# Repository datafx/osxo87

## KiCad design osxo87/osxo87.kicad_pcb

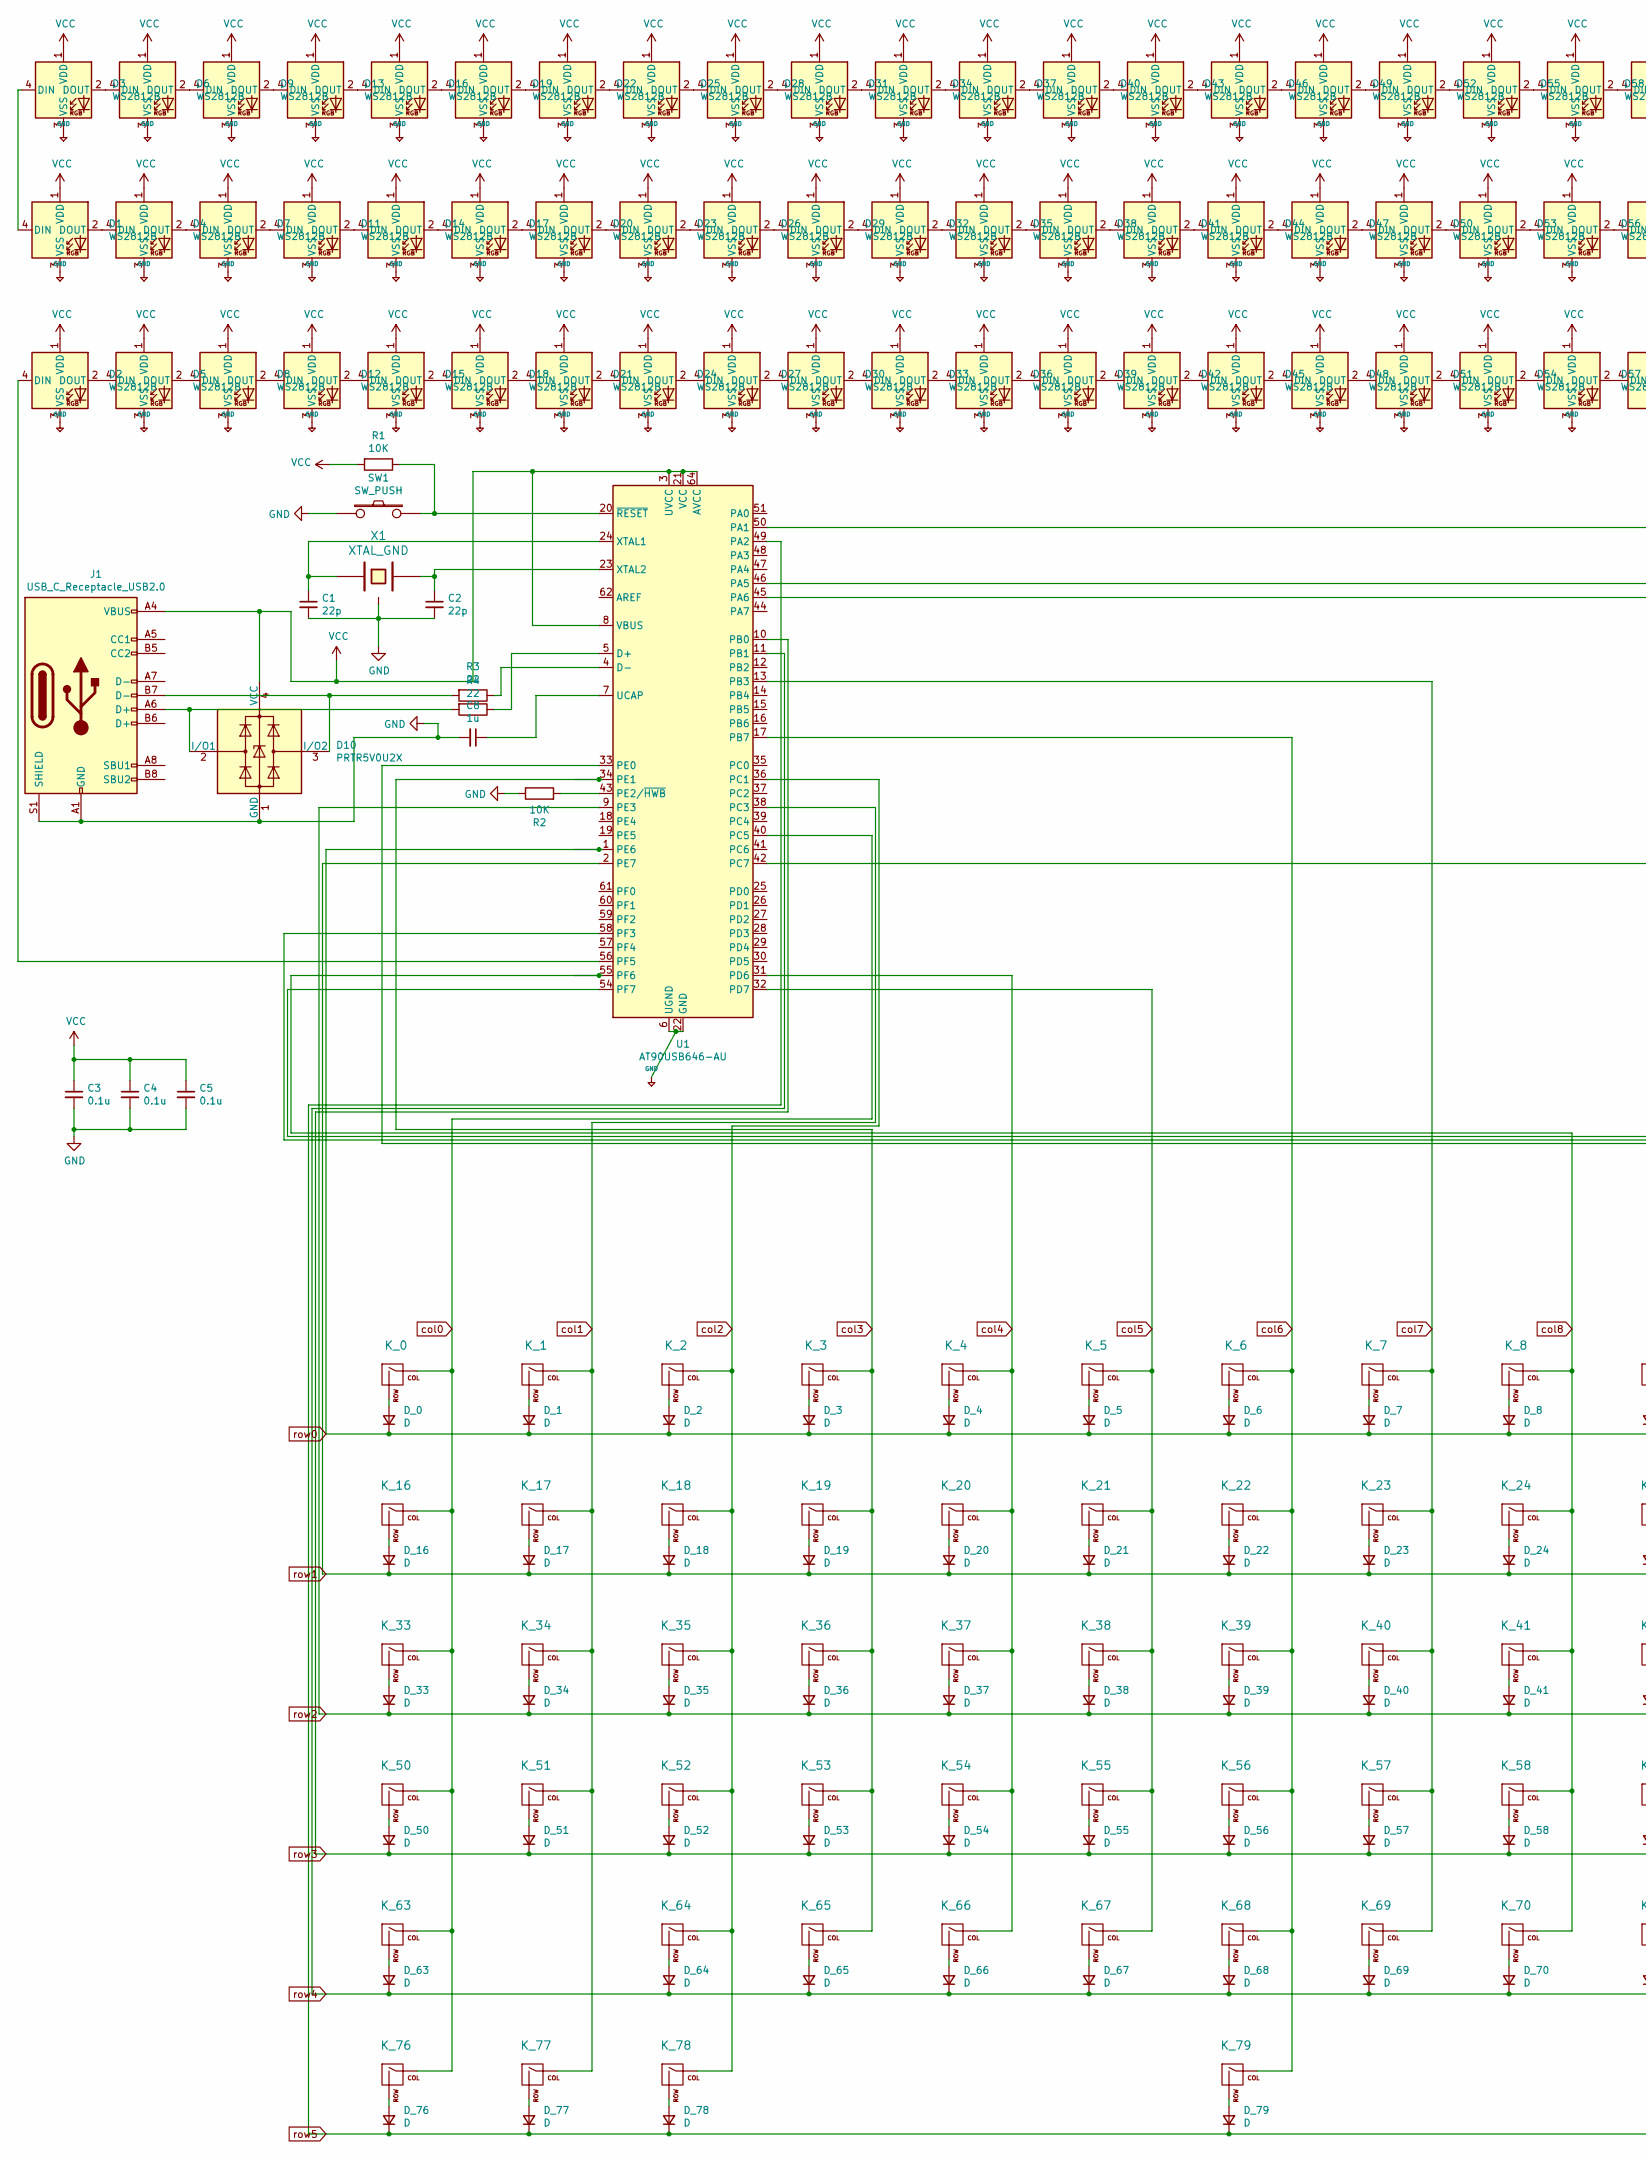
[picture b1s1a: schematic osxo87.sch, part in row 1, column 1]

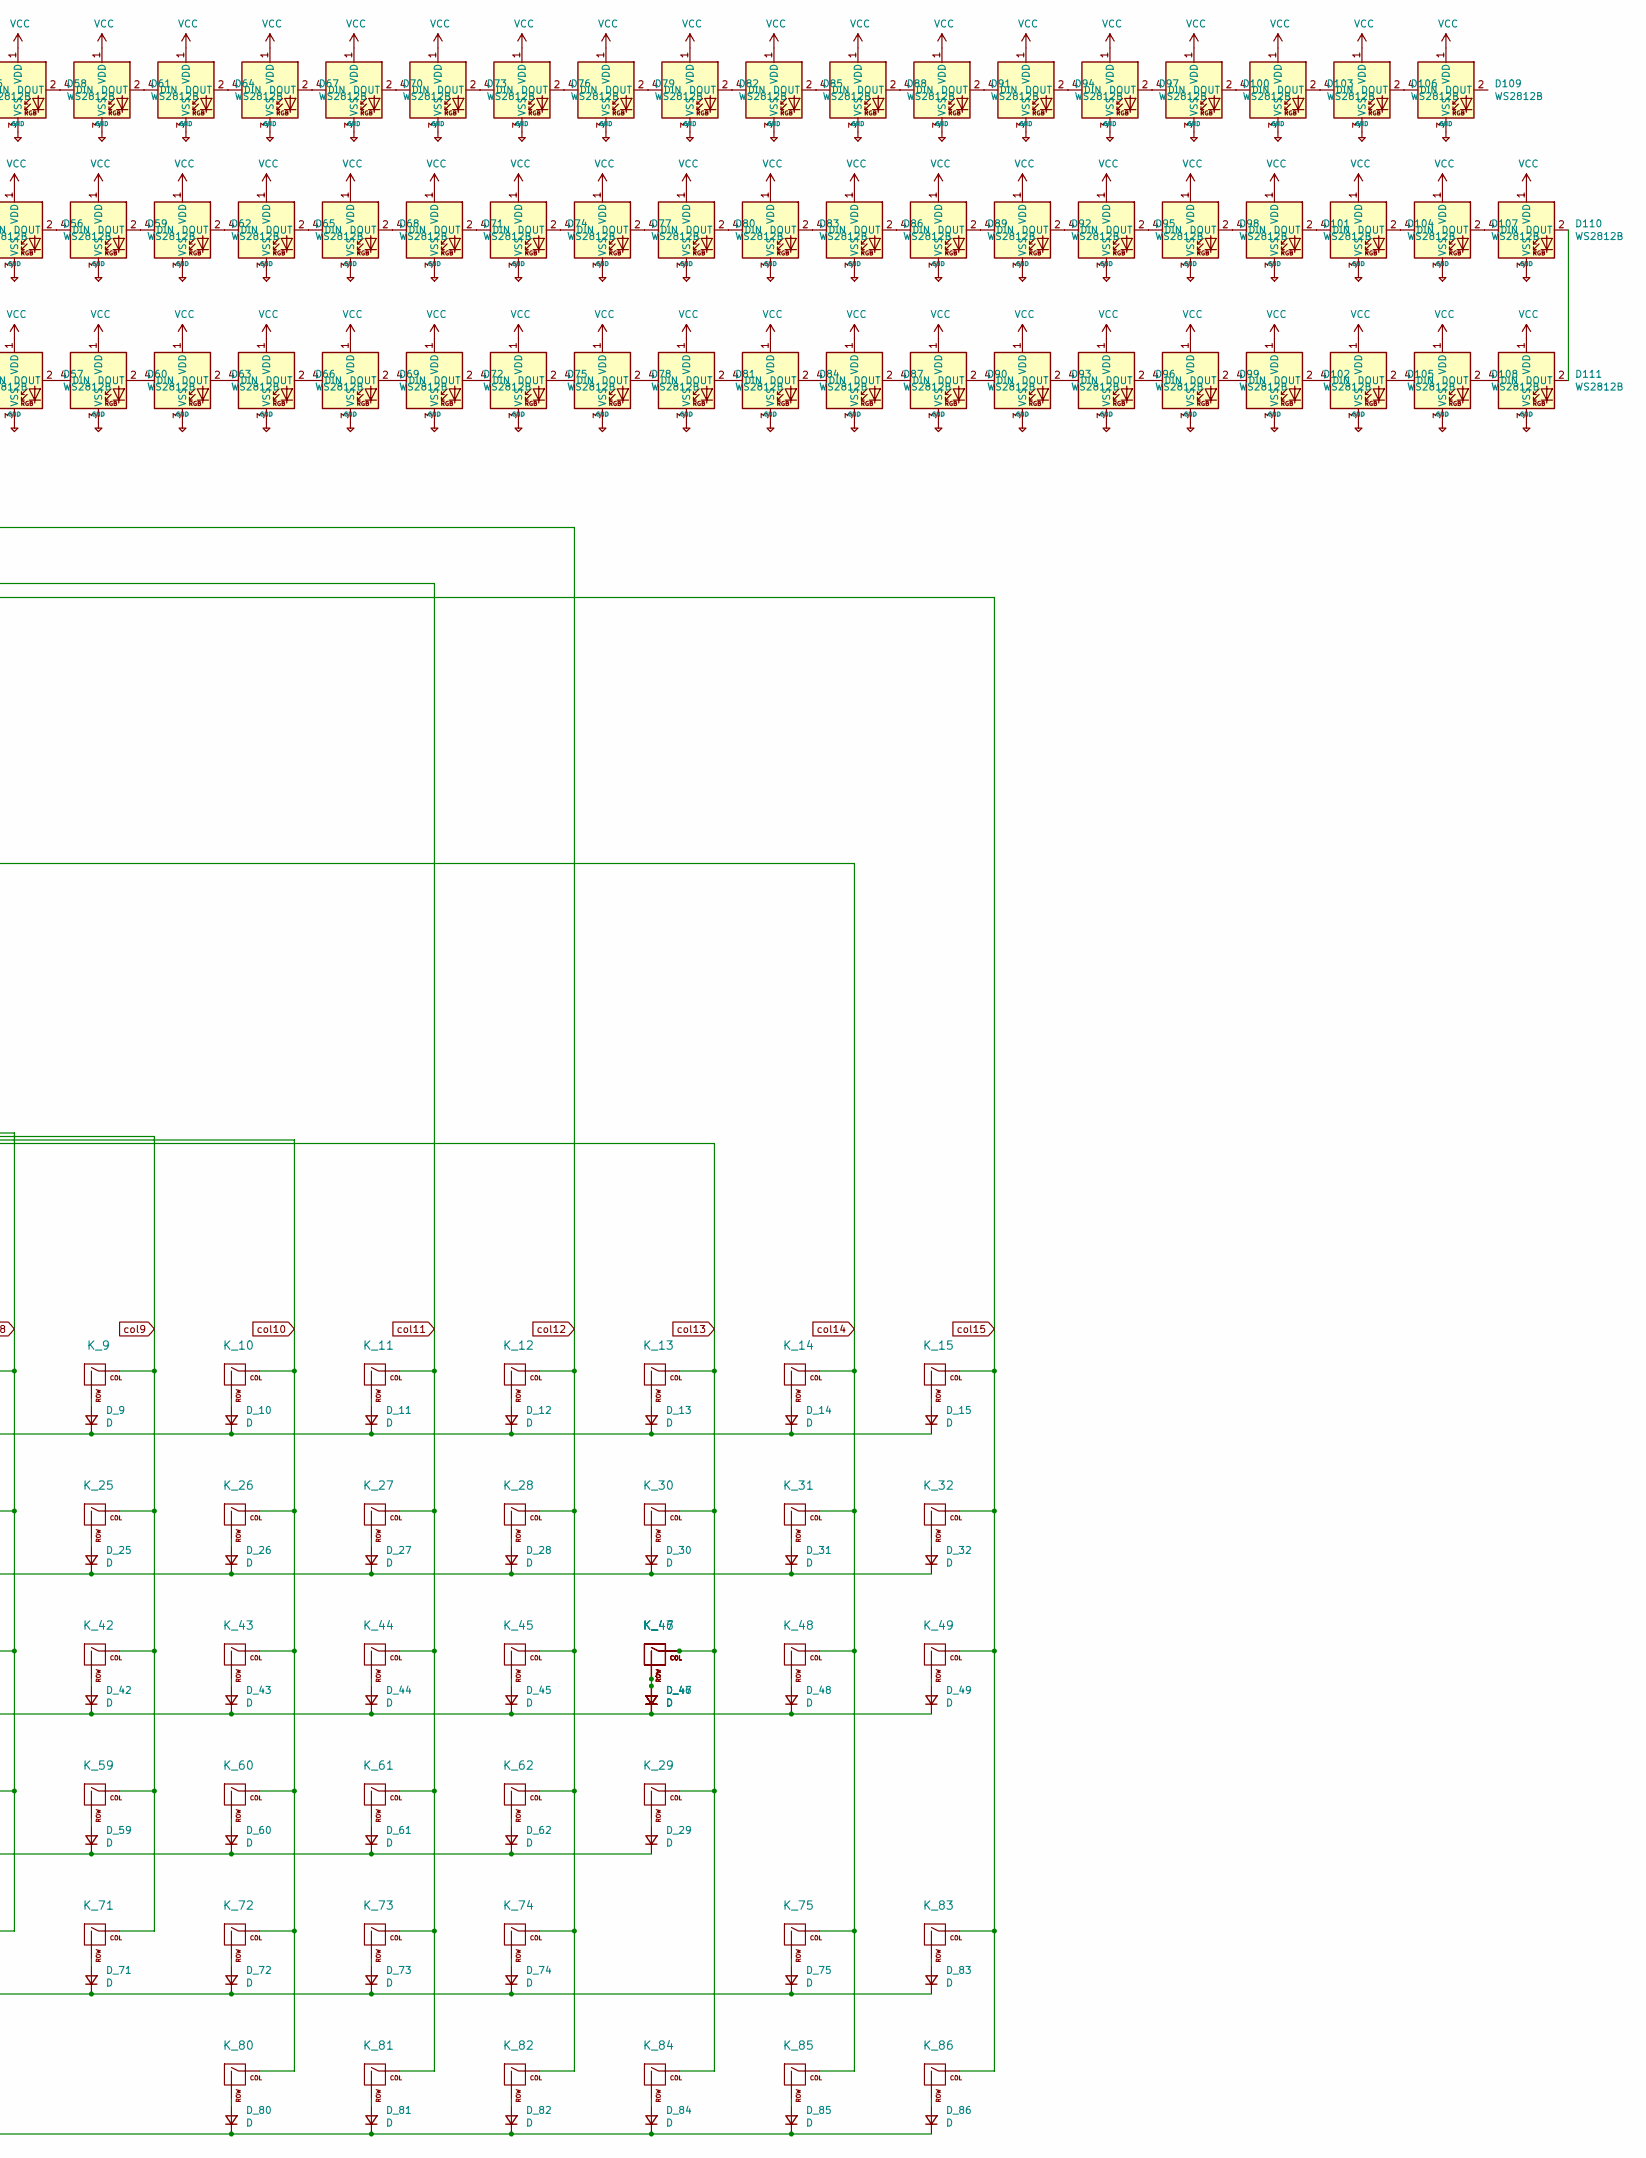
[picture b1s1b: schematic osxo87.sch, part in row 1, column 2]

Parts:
C1, C2: 22p; C_0805_2012Metric
C3, C4, C5: 0.1u; C_0805_2012Metric
C8: 1u; C_0805_2012Metric
D1, D2, D3, D4, D5, D6, D7, D8, D9, D11, D12, D13, D14, D15, D16, D17, D18, D19, D20, D21, D22, D23, D24, D25, D26, D27, D28, D29, D30, D31, D32, D33, D34, D35, D36, D37, D38, D39, D40, D41, D42, D43, D44, D45, D46, D47, D48, D49, D50, D51, D52, D53, D54, D55, D56, D57, D58, D59, D60, D61, D62, D63, D64, D65, D66, D67, D68, D69, D70, D71, D72, D73, D74, D75, D76, D77, D78, D79, D80, D81, D82, D83, D84, D85, D86, D87, D88, D89, D90, D91, D92, D93, D94, D95, D96, D97, D98, D99, D100, D101, D102, D103, D104, D105, D106, D107, D108, D109, D110, D111: WS2812B; LED_WS2812B_PLCC4_5.0x5.0mm_P3.2mm
D10: PRTR5V0U2X; SOT-143
D_0, D_1, D_2, D_3, D_4, D_5, D_6, D_7, D_8, D_9, D_10, D_11, D_12, D_13, D_14, D_15, D_16, D_17, D_18, D_19, D_20, D_21, D_22, D_23, D_24, D_25, D_26, D_27, D_28, D_29, D_30, D_31, D_32, D_33, D_34, D_35, D_36, D_37, D_38, D_39, D_40, D_41, D_42, D_43, D_44, D_45, D_46, D_47, D_48, D_49, D_50, D_51, D_52, D_53, D_54, D_55, D_56, D_57, D_58, D_59, D_60, D_61, D_62, D_63, D_64, D_65, D_66, D_67, D_68, D_69, D_70, D_71, D_72, D_73, D_74, D_75, D_76, D_77, D_78, D_79, D_80, D_81, D_82, D_83, D_84, D_85, D_86: D; D_SOD-123
J1: USB_C_Receptacle_USB2.0; USB_C_Receptacle_Palconn_UTC16-G
K_0, K_1, K_2, K_3, K_4, K_5, K_6, K_7, K_8, K_9, K_10, K_11, K_12, K_13, K_14, K_15, K_16, K_17, K_18, K_19, K_20, K_21, K_22, K_23, K_24, K_25, K_26, K_27, K_28, K_30, K_31, K_32, K_34, K_35, K_36, K_37, K_38, K_39, K_40, K_41, K_42, K_43, K_44, K_45, K_47, K_48, K_49, K_51, K_52, K_53, K_54, K_55, K_56, K_57, K_58, K_59, K_60, K_61, K_64, K_65, K_66, K_67, K_68, K_69, K_70, K_71, K_72, K_73, K_75, K_84, K_85, K_86: KEYSW; MX-1U-NoLED
K_29: KEYSW; MX-2U-NoLED
K_33, K_46: KEYSW; MX-1.5U-NoLED
K_50: KEYSW; MX-1.75U-NoLED
K_62, K_63: KEYSW; MX-2.25U-NoLED
K_74: KEYSW; MX-2.75U-NoLED
K_76, K_77, K_78, K_80, K_81, K_82, K_83: KEYSW; MX-1.25U-NoLED
K_79: KEYSW; MX-6.25U-NoLED
R1, R2: 10K; R_0805_2012Metric
R3, R4: 22; R_0805_2012Metric
SW1: SW_PUSH; Panasonic_EVQPUJ_EVQPUA
U1: AT90USB646-AU; TQFP-64_14x14mm_P0.8mm
X1: XTAL_GND; Crystal_SMD_0603-4Pin_6.0x3.5mm

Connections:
unnamed: C1.1, U1.24 (XTAL1), X1.1
unnamed: C2.1, U1.23 (XTAL2), X1.2
unnamed: C8.1, U1.7 (UCAP)
unnamed: D1.2 (DOUT), D4.4 (DIN)
unnamed: D1.4 (DIN), D3.4 (DIN)
unnamed: D2.2 (DOUT), D5.4 (DIN)
unnamed: D2.4 (DIN), U1.56 (PF5)
unnamed: D3.2 (DOUT), D6.4 (DIN)
unnamed: D4.2 (DOUT), D7.4 (DIN)
unnamed: D5.2 (DOUT), D8.4 (DIN)
unnamed: D6.2 (DOUT), D9.4 (DIN)
unnamed: D10.2 (I/O1), J1.A6 (D+), R4.2
unnamed: D10.3 (I/O2), J1.B7 (D-), R3.2
unnamed: D11.2 (DOUT), D14.4 (DIN)
unnamed: D7.2 (DOUT), D11.4 (DIN)
unnamed: D12.2 (DOUT), D15.4 (DIN)
unnamed: D8.2 (DOUT), D12.4 (DIN)
unnamed: D13.2 (DOUT), D16.4 (DIN)
unnamed: D9.2 (DOUT), D13.4 (DIN)
unnamed: D14.2 (DOUT), D17.4 (DIN)
unnamed: D15.2 (DOUT), D18.4 (DIN)
unnamed: D16.2 (DOUT), D19.4 (DIN)
unnamed: D17.2 (DOUT), D20.4 (DIN)
unnamed: D18.2 (DOUT), D21.4 (DIN)
unnamed: D19.2 (DOUT), D22.4 (DIN)
unnamed: D20.2 (DOUT), D23.4 (DIN)
unnamed: D21.2 (DOUT), D24.4 (DIN)
unnamed: D22.2 (DOUT), D25.4 (DIN)
unnamed: D23.2 (DOUT), D26.4 (DIN)
unnamed: D24.2 (DOUT), D27.4 (DIN)
unnamed: D25.2 (DOUT), D28.4 (DIN)
unnamed: D26.2 (DOUT), D29.4 (DIN)
unnamed: D27.2 (DOUT), D30.4 (DIN)
unnamed: D28.2 (DOUT), D31.4 (DIN)
unnamed: D29.2 (DOUT), D32.4 (DIN)
unnamed: D30.2 (DOUT), D33.4 (DIN)
unnamed: D31.2 (DOUT), D34.4 (DIN)
unnamed: D32.2 (DOUT), D35.4 (DIN)
unnamed: D33.2 (DOUT), D36.4 (DIN)
unnamed: D34.2 (DOUT), D37.4 (DIN)
unnamed: D35.2 (DOUT), D38.4 (DIN)
unnamed: D36.2 (DOUT), D39.4 (DIN)
unnamed: D37.2 (DOUT), D40.4 (DIN)
unnamed: D38.2 (DOUT), D41.4 (DIN)
unnamed: D39.2 (DOUT), D42.4 (DIN)
unnamed: D40.2 (DOUT), D43.4 (DIN)
unnamed: D41.2 (DOUT), D44.4 (DIN)
unnamed: D42.2 (DOUT), D45.4 (DIN)
unnamed: D43.2 (DOUT), D46.4 (DIN)
unnamed: D44.2 (DOUT), D47.4 (DIN)
unnamed: D45.2 (DOUT), D48.4 (DIN)
unnamed: D46.2 (DOUT), D49.4 (DIN)
unnamed: D47.2 (DOUT), D50.4 (DIN)
unnamed: D48.2 (DOUT), D51.4 (DIN)
unnamed: D49.2 (DOUT), D52.4 (DIN)
unnamed: D50.2 (DOUT), D53.4 (DIN)
unnamed: D51.2 (DOUT), D54.4 (DIN)
unnamed: D52.2 (DOUT), D55.4 (DIN)
unnamed: D53.2 (DOUT), D56.4 (DIN)
unnamed: D54.2 (DOUT), D57.4 (DIN)
unnamed: D55.2 (DOUT), D58.4 (DIN)
unnamed: D56.2 (DOUT), D59.4 (DIN)
unnamed: D57.2 (DOUT), D60.4 (DIN)
unnamed: D58.2 (DOUT), D61.4 (DIN)
unnamed: D59.2 (DOUT), D62.4 (DIN)
unnamed: D60.2 (DOUT), D63.4 (DIN)
unnamed: D61.2 (DOUT), D64.4 (DIN)
unnamed: D62.2 (DOUT), D65.4 (DIN)
unnamed: D63.2 (DOUT), D66.4 (DIN)
unnamed: D64.2 (DOUT), D67.4 (DIN)
unnamed: D65.2 (DOUT), D68.4 (DIN)
unnamed: D66.2 (DOUT), D69.4 (DIN)
unnamed: D67.2 (DOUT), D70.4 (DIN)
unnamed: D68.2 (DOUT), D71.4 (DIN)
unnamed: D69.2 (DOUT), D72.4 (DIN)
unnamed: D70.2 (DOUT), D73.4 (DIN)
unnamed: D71.2 (DOUT), D74.4 (DIN)
unnamed: D72.2 (DOUT), D75.4 (DIN)
unnamed: D73.2 (DOUT), D76.4 (DIN)
unnamed: D74.2 (DOUT), D77.4 (DIN)
unnamed: D75.2 (DOUT), D78.4 (DIN)
unnamed: D76.2 (DOUT), D79.4 (DIN)
unnamed: D77.2 (DOUT), D80.4 (DIN)
unnamed: D78.2 (DOUT), D81.4 (DIN)
unnamed: D79.2 (DOUT), D82.4 (DIN)
unnamed: D80.2 (DOUT), D83.4 (DIN)
unnamed: D81.2 (DOUT), D84.4 (DIN)
unnamed: D82.2 (DOUT), D85.4 (DIN)
unnamed: D83.2 (DOUT), D86.4 (DIN)
unnamed: D84.2 (DOUT), D87.4 (DIN)
unnamed: D85.2 (DOUT), D88.4 (DIN)
unnamed: D86.2 (DOUT), D89.4 (DIN)
unnamed: D87.2 (DOUT), D90.4 (DIN)
unnamed: D88.2 (DOUT), D91.4 (DIN)
unnamed: D89.2 (DOUT), D92.4 (DIN)
unnamed: D90.2 (DOUT), D93.4 (DIN)
unnamed: D91.2 (DOUT), D94.4 (DIN)
unnamed: D92.2 (DOUT), D95.4 (DIN)
unnamed: D93.2 (DOUT), D96.4 (DIN)
unnamed: D94.2 (DOUT), D97.4 (DIN)
unnamed: D95.2 (DOUT), D98.4 (DIN)
unnamed: D96.2 (DOUT), D99.4 (DIN)
unnamed: D100.2 (DOUT), D103.4 (DIN)
unnamed: D97.2 (DOUT), D100.4 (DIN)
unnamed: D101.2 (DOUT), D104.4 (DIN)
unnamed: D98.2 (DOUT), D101.4 (DIN)
unnamed: D102.2 (DOUT), D105.4 (DIN)
unnamed: D99.2 (DOUT), D102.4 (DIN)
unnamed: D103.2 (DOUT), D106.4 (DIN)
unnamed: D104.2 (DOUT), D107.4 (DIN)
unnamed: D105.2 (DOUT), D108.4 (DIN)
unnamed: D106.2 (DOUT), D109.4 (DIN)
unnamed: D107.2 (DOUT), D110.4 (DIN)
unnamed: D108.2 (DOUT), D111.4 (DIN)
unnamed: D110.2 (DOUT), D111.2 (DOUT)
unnamed: D_0.2 (A), K_0.2 (ROW)
unnamed: D_1.2 (A), K_1.2 (ROW)
unnamed: D_2.2 (A), K_2.2 (ROW)
unnamed: D_3.2 (A), K_3.2 (ROW)
unnamed: D_4.2 (A), K_4.2 (ROW)
unnamed: D_5.2 (A), K_5.2 (ROW)
unnamed: D_6.2 (A), K_6.2 (ROW)
unnamed: D_7.2 (A), K_7.2 (ROW)
unnamed: D_8.2 (A), K_8.2 (ROW)
unnamed: D_9.2 (A), K_9.2 (ROW)
unnamed: D_10.2 (A), K_10.2 (ROW)
unnamed: D_11.2 (A), K_11.2 (ROW)
unnamed: D_12.2 (A), K_12.2 (ROW)
unnamed: D_13.2 (A), K_13.2 (ROW)
unnamed: D_14.2 (A), K_14.2 (ROW)
unnamed: D_15.2 (A), K_15.2 (ROW)
unnamed: D_16.2 (A), K_16.2 (ROW)
unnamed: D_17.2 (A), K_17.2 (ROW)
unnamed: D_18.2 (A), K_18.2 (ROW)
unnamed: D_19.2 (A), K_19.2 (ROW)
unnamed: D_20.2 (A), K_20.2 (ROW)
unnamed: D_21.2 (A), K_21.2 (ROW)
unnamed: D_22.2 (A), K_22.2 (ROW)
unnamed: D_23.2 (A), K_23.2 (ROW)
unnamed: D_24.2 (A), K_24.2 (ROW)
unnamed: D_25.2 (A), K_25.2 (ROW)
unnamed: D_26.2 (A), K_26.2 (ROW)
unnamed: D_27.2 (A), K_27.2 (ROW)
unnamed: D_28.2 (A), K_28.2 (ROW)
unnamed: D_29.2 (A), K_29.2 (ROW)
unnamed: D_30.2 (A), K_30.2 (ROW)
unnamed: D_31.2 (A), K_31.2 (ROW)
unnamed: D_32.2 (A), K_32.2 (ROW)
unnamed: D_33.2 (A), K_33.2 (ROW)
unnamed: D_34.2 (A), K_34.2 (ROW)
unnamed: D_35.2 (A), K_35.2 (ROW)
unnamed: D_36.2 (A), K_36.2 (ROW)
unnamed: D_37.2 (A), K_37.2 (ROW)
unnamed: D_38.2 (A), K_38.2 (ROW)
unnamed: D_39.2 (A), K_39.2 (ROW)
unnamed: D_40.2 (A), K_40.2 (ROW)
unnamed: D_41.2 (A), K_41.2 (ROW)
unnamed: D_42.2 (A), K_42.2 (ROW)
unnamed: D_43.2 (A), K_43.2 (ROW)
unnamed: D_44.2 (A), K_44.2 (ROW)
unnamed: D_45.2 (A), K_45.2 (ROW)
unnamed: D_46.2 (A), D_47.2 (A), K_46.2 (ROW), K_47.2 (ROW)
unnamed: D_48.2 (A), K_48.2 (ROW)
unnamed: D_49.2 (A), K_49.2 (ROW)
unnamed: D_50.2 (A), K_50.2 (ROW)
unnamed: D_51.2 (A), K_51.2 (ROW)
unnamed: D_52.2 (A), K_52.2 (ROW)
unnamed: D_53.2 (A), K_53.2 (ROW)
unnamed: D_54.2 (A), K_54.2 (ROW)
unnamed: D_55.2 (A), K_55.2 (ROW)
unnamed: D_56.2 (A), K_56.2 (ROW)
unnamed: D_57.2 (A), K_57.2 (ROW)
unnamed: D_58.2 (A), K_58.2 (ROW)
unnamed: D_59.2 (A), K_59.2 (ROW)
unnamed: D_60.2 (A), K_60.2 (ROW)
unnamed: D_61.2 (A), K_61.2 (ROW)
unnamed: D_62.2 (A), K_62.2 (ROW)
unnamed: D_63.2 (A), K_63.2 (ROW)
unnamed: D_64.2 (A), K_64.2 (ROW)
unnamed: D_65.2 (A), K_65.2 (ROW)
unnamed: D_66.2 (A), K_66.2 (ROW)
unnamed: D_67.2 (A), K_67.2 (ROW)
unnamed: D_68.2 (A), K_68.2 (ROW)
unnamed: D_69.2 (A), K_69.2 (ROW)
unnamed: D_70.2 (A), K_70.2 (ROW)
unnamed: D_71.2 (A), K_71.2 (ROW)
unnamed: D_72.2 (A), K_72.2 (ROW)
unnamed: D_73.2 (A), K_73.2 (ROW)
unnamed: D_74.2 (A), K_74.2 (ROW)
unnamed: D_75.2 (A), K_75.2 (ROW)
unnamed: D_76.2 (A), K_76.2 (ROW)
unnamed: D_77.2 (A), K_77.2 (ROW)
unnamed: D_78.2 (A), K_78.2 (ROW)
unnamed: D_79.2 (A), K_79.2 (ROW)
unnamed: D_80.2 (A), K_80.2 (ROW)
unnamed: D_81.2 (A), K_81.2 (ROW)
unnamed: D_82.2 (A), K_82.2 (ROW)
unnamed: D_83.2 (A), K_83.2 (ROW)
unnamed: D_84.2 (A), K_84.2 (ROW)
unnamed: D_85.2 (A), K_85.2 (ROW)
unnamed: D_86.2 (A), K_86.2 (ROW)
unnamed: R1.1, SW1.2, U1.20 (~RESET)
unnamed: R2.2, U1.43 (PE2/~HWB)
unnamed: R3.1, U1.4 (D-)
unnamed: R4.1, U1.5 (D+)
VCC: C3.1, C4.1, C5.1, D1.1 (VDD), D2.1 (VDD), D3.1 (VDD), D4.1 (VDD), D5.1 (VDD), D6.1 (VDD), D7.1 (VDD), D8.1 (VDD), D9.1 (VDD), D10.4 (VCC), D11.1 (VDD), D12.1 (VDD), D13.1 (VDD), D14.1 (VDD), D15.1 (VDD), D16.1 (VDD), D17.1 (VDD), D18.1 (VDD), D19.1 (VDD), D20.1 (VDD), D21.1 (VDD), D22.1 (VDD), D23.1 (VDD), D24.1 (VDD), D25.1 (VDD), D26.1 (VDD), D27.1 (VDD), D28.1 (VDD), D29.1 (VDD), D30.1 (VDD), D31.1 (VDD), D32.1 (VDD), D33.1 (VDD), D34.1 (VDD), D35.1 (VDD), D36.1 (VDD), D37.1 (VDD), D38.1 (VDD), D39.1 (VDD), D40.1 (VDD), D41.1 (VDD), D42.1 (VDD), D43.1 (VDD), D44.1 (VDD), D45.1 (VDD), D46.1 (VDD), D47.1 (VDD), D48.1 (VDD), D49.1 (VDD), D50.1 (VDD), D51.1 (VDD), D52.1 (VDD), D53.1 (VDD), D54.1 (VDD), D55.1 (VDD), D56.1 (VDD), D57.1 (VDD), D58.1 (VDD), D59.1 (VDD), D60.1 (VDD), D61.1 (VDD), D62.1 (VDD), D63.1 (VDD), D64.1 (VDD), D65.1 (VDD), D66.1 (VDD), D67.1 (VDD), D68.1 (VDD), D69.1 (VDD), D70.1 (VDD), D71.1 (VDD), D72.1 (VDD), D73.1 (VDD), D74.1 (VDD), D75.1 (VDD), D76.1 (VDD), D77.1 (VDD), D78.1 (VDD), D79.1 (VDD), D80.1 (VDD), D81.1 (VDD), D82.1 (VDD), D83.1 (VDD), D84.1 (VDD), D85.1 (VDD), D86.1 (VDD), D87.1 (VDD), D88.1 (VDD), D89.1 (VDD), D90.1 (VDD), D91.1 (VDD), D92.1 (VDD), D93.1 (VDD), D94.1 (VDD), D95.1 (VDD), D96.1 (VDD), D97.1 (VDD), D98.1 (VDD), D99.1 (VDD), D100.1 (VDD), D101.1 (VDD), D102.1 (VDD), D103.1 (VDD), D104.1 (VDD), D105.1 (VDD), D106.1 (VDD), D107.1 (VDD), D108.1 (VDD), D109.1 (VDD), D110.1 (VDD), D111.1 (VDD), J1.A4 (VBUS), J1.A9 (VBUS), J1.B4 (VBUS), J1.B9 (VBUS), R1.2, U1.3 (UVCC), U1.8 (VBUS), U1.21 (VCC), U1.52 (VCC), U1.64 (AVCC)
col0: K_0.1 (COL), K_16.1 (COL), K_33.1 (COL), K_50.1 (COL), K_63.1 (COL), K_76.1 (COL), U1.40 (PC5)
col1: K_1.1 (COL), K_17.1 (COL), K_34.1 (COL), K_51.1 (COL), K_77.1 (COL), U1.38 (PC3)
col2: K_2.1 (COL), K_18.1 (COL), K_35.1 (COL), K_52.1 (COL), K_64.1 (COL), K_78.1 (COL), U1.36 (PC1)
col3: K_3.1 (COL), K_19.1 (COL), K_36.1 (COL), K_53.1 (COL), K_65.1 (COL), U1.34 (PE1)
col4: K_4.1 (COL), K_20.1 (COL), K_37.1 (COL), K_54.1 (COL), K_66.1 (COL), U1.31 (PD6)
col5: K_5.1 (COL), K_21.1 (COL), K_38.1 (COL), K_55.1 (COL), K_67.1 (COL), U1.32 (PD7)
col6: K_6.1 (COL), K_22.1 (COL), K_39.1 (COL), K_56.1 (COL), K_68.1 (COL), K_79.1 (COL), U1.17 (PB7)
col7: K_7.1 (COL), K_23.1 (COL), K_40.1 (COL), K_57.1 (COL), K_69.1 (COL), U1.13 (PB3)
col8: K_8.1 (COL), K_24.1 (COL), K_41.1 (COL), K_58.1 (COL), K_70.1 (COL), U1.55 (PF6)
col9: K_9.1 (COL), K_25.1 (COL), K_42.1 (COL), K_59.1 (COL), K_71.1 (COL), U1.54 (PF7)
col10: K_10.1 (COL), K_26.1 (COL), K_43.1 (COL), K_60.1 (COL), K_72.1 (COL), K_80.1 (COL), U1.58 (PF3)
col11: K_11.1 (COL), K_27.1 (COL), K_44.1 (COL), K_61.1 (COL), K_73.1 (COL), K_81.1 (COL), U1.46 (PA5)
col12: K_12.1 (COL), K_28.1 (COL), K_45.1 (COL), K_62.1 (COL), K_74.1 (COL), K_82.1 (COL), U1.50 (PA1)
col13: K_13.1 (COL), K_29.1 (COL), K_30.1 (COL), K_46.1 (COL), K_47.1 (COL), K_84.1 (COL), U1.33 (PE0)
col14: K_14.1 (COL), K_31.1 (COL), K_48.1 (COL), K_75.1 (COL), K_85.1 (COL), U1.42 (PC7)
col15: K_15.1 (COL), K_32.1 (COL), K_49.1 (COL), K_83.1 (COL), K_86.1 (COL), U1.45 (PA6)
row0: D_0.1 (K), D_1.1 (K), D_2.1 (K), D_3.1 (K), D_4.1 (K), D_5.1 (K), D_6.1 (K), D_7.1 (K), D_8.1 (K), D_9.1 (K), D_10.1 (K), D_11.1 (K), D_12.1 (K), D_13.1 (K), D_14.1 (K), D_15.1 (K), U1.1 (PE6)
row1: D_16.1 (K), D_17.1 (K), D_18.1 (K), D_19.1 (K), D_20.1 (K), D_21.1 (K), D_22.1 (K), D_23.1 (K), D_24.1 (K), D_25.1 (K), D_26.1 (K), D_27.1 (K), D_28.1 (K), D_30.1 (K), D_31.1 (K), D_32.1 (K), U1.2 (PE7)
row2: D_33.1 (K), D_34.1 (K), D_35.1 (K), D_36.1 (K), D_37.1 (K), D_38.1 (K), D_39.1 (K), D_40.1 (K), D_41.1 (K), D_42.1 (K), D_43.1 (K), D_44.1 (K), D_45.1 (K), D_46.1 (K), D_47.1 (K), D_48.1 (K), D_49.1 (K), U1.9 (PE3)
row3: D_29.1 (K), D_50.1 (K), D_51.1 (K), D_52.1 (K), D_53.1 (K), D_54.1 (K), D_55.1 (K), D_56.1 (K), D_57.1 (K), D_58.1 (K), D_59.1 (K), D_60.1 (K), D_61.1 (K), D_62.1 (K), U1.10 (PB0)
row4: D_63.1 (K), D_64.1 (K), D_65.1 (K), D_66.1 (K), D_67.1 (K), D_68.1 (K), D_69.1 (K), D_70.1 (K), D_71.1 (K), D_72.1 (K), D_73.1 (K), D_74.1 (K), D_75.1 (K), D_83.1 (K), U1.11 (PB1)
row5: D_76.1 (K), D_77.1 (K), D_78.1 (K), D_79.1 (K), D_80.1 (K), D_81.1 (K), D_82.1 (K), D_84.1 (K), D_85.1 (K), D_86.1 (K), U1.49 (PA2)

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
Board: 2 copper layers, 299 parts (87 on the bottom side), 230 nets, no tracks yet.

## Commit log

2021-02-10 initial
2021-02-10 add submodules
2021-02-10 libraries
